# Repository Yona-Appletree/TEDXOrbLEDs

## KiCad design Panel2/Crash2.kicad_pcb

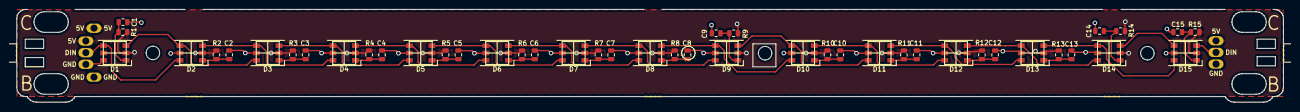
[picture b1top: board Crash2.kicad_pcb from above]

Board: 4 copper layers, 279.2 x 20.2 mm, 47 parts (0 on the bottom side), 33 nets.

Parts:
C1, C2, C3, C4, C5, C6, C7, C8, C9, C10, C11, C12, C13, C14, C15: 100NF; C_0805_2012Metric
D1, D2, D3, D4, D5, D6, D7, D8, D9, D10, D11, D12, D13, D14, D15: WS2813; LED_WS2812_PLCC6_5.0x5.0mm_P1.6mm
J1: IN; 1x3_18awgWireSolderPad-InsideStrut
J2: OUT; 1x3_18awgWireSolderPad-InsideStrut-OUT
R1, R2, R3, R4, R5, R6, R7, R8, R9, R10, R11, R12, R13, R14, R15: 330; R_0805_2012Metric

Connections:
+5V: D1.2, D2.2, D3.2, D4.2, D5.2, D6.2, D7.2, D8.2, D9.2, D10.2, D11.2, D12.2, D13.2, D14.2, D15.2, J1.1, J2.1, R1.1, R2.1, R3.1, R4.1, R5.1, R6.1, R7.1, R8.1, R9.1, R10.1, R11.1, R12.1, R13.1, R14.1, R15.1
GND: C1.2, C2.2, C3.2, C4.2, C5.2, C6.2, C7.2, C8.2, C9.2, C10.2, C11.2, C12.2, C13.2, C14.2, C15.2, D1.5, D1.6, D2.5, D3.5, D4.5, D5.5, D6.5, D7.5, D8.5, D9.5, D10.5, D11.5, D12.5, D13.5, D14.5, D15.5, J1.3, J2.3
unnamed: C1.1, D1.1, R1.2
unnamed: C2.1, D2.1, R2.2
unnamed: C3.1, D3.1, R3.2
unnamed: C4.1, D4.1, R4.2
unnamed: C5.1, D5.1, R5.2
unnamed: C6.1, D6.1, R6.2
unnamed: C7.1, D7.1, R7.2
unnamed: C8.1, D8.1, R8.2
unnamed: C9.1, D9.1, R9.2
unnamed: C10.1, D10.1, R10.2
unnamed: C11.1, D11.1, R11.2
unnamed: C12.1, D12.1, R12.2
unnamed: C13.1, D13.1, R13.2
unnamed: C14.1, D14.1, R14.2
unnamed: C15.1, D15.1, R15.2
unnamed: D1.3, D2.4, D3.6
unnamed: D1.4, D2.6, J1.2
unnamed: D2.3, D3.4, D4.6
unnamed: D3.3, D4.4, D5.6
unnamed: D4.3, D5.4, D6.6
unnamed: D5.3, D6.4, D7.6
unnamed: D6.3, D7.4, D8.6
unnamed: D7.3, D8.4, D9.6
unnamed: D10.3, D11.4, D12.6
unnamed: D9.3, D10.4, D11.6
unnamed: D8.3, D9.4, D10.6
unnamed: D11.3, D12.4, D13.6
unnamed: D12.3, D13.4, D14.6
unnamed: D13.3, D14.4, D15.6
unnamed: D14.3, D15.4
unnamed: D15.3, J2.2

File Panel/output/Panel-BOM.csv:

"Id","Designator","Package","Quantity","Designation","Supplier and ref",
4,"R2,R3,R4,R5,R6,R7,R8,R9,R10,R11,R12,R1,R13,R14,R15,R2,R3,R4,R5,R6,R7,R8,R9,R10,R11,R12,R16,R1,R13,R14,R15,R2,R3,R4,R5,R6,R7,R8,R9,R10,R11,R12,R16,R1,R13,R14,R15,R1,R13,R14,R15,R2,R3,R4,R5,R6,R7,R8,R9,R10,R11,R12,R2,R3,R4,R5,R6,R7,R8,R9,R10,R11,R12,R1,R13,R14,R15,R2,R3,R4,R5,R6,R7,R8,R9,R10,R11,R12,R16,R1,R13,R14,R15,R2,R3,R4,R5,R6,R7,R8,R9,R10,R11,R12,R16,R1,R13,R14,R15,R2,R3,R4,R5,R6,R7,R8,R9,R10,R11,R12,R1,R13,R14,R15,R16,R17,R2,R3,R4,R5,R6,R7,R8,R9,R10,R11,R12,R13,R14,R15,R16,R17,R1,R2,R3,R4,R5,R6,R7,R8,R9,R10,R11,R12,R16,R1,R13,R14,R15,R2,R3,R4,R5,R6,R7,R8,R9,R10,R11,R12,R16,R1,R13,R14,R15,R2,R3,R4,R5,R6,R7,R8,R9,R10,R11,R12,R1,R2,R3,R4,R5,R6,R7,R8,R9,R10,R11,R12,R1,R13,R14,R15,R1,R2,R3,R4,R5,R6,R7,R8,R9,R10,R11,R12","R_0805_2012Metric",214,"330",,,
5,"C7,C6,C5,C4,C3,C2,C1,C13,C14,C15,C8,C9,C10,C11,C12,C7,C6,C5,C4,C3,C2,C1,C13,C14,C15,C16,C8,C9,C10,C11,C12,C7,C6,C5,C4,C3,C2,C1,C10,C11,C12,C9,C15,C13,C14,C16,C8,C14,C13,C1,C3,C2,C4,C5,C6,C15,C8,C9,C10,C11,C12,C7,C7,C6,C5,C4,C3,C2,C1,C13,C14,C15,C8,C9,C10,C11,C12,C7,C6,C5,C4,C3,C2,C1,C13,C14,C15,C16,C8,C9,C10,C11,C12,C7,C6,C5,C4,C3,C2,C1,C15,C13,C14,C16,C8,C9,C10,C11,C12,C7,C6,C5,C4,C3,C2,C1,C13,C14,C15,C16,C17,C8,C9,C10,C11,C12,C7,C6,C5,C4,C3,C2,C1,C17,C13,C14,C15,C16,C8,C9,C10,C11,C12,C7,C6,C5,C4,C3,C2,C1,C13,C14,C15,C16,C8,C9,C10,C11,C12,C7,C6,C5,C4,C3,C2,C1,C13,C14,C15,C16,C8,C9,C10,C11,C12,C7,C6,C5,C4,C3,C2,C1,C7,C6,C5,C4,C3,C2,C1,C13,C14,C15,C8,C9,C10,C11,C12,C8,C9,C10,C11,C12,C7,C6,C5,C4,C3,C2,C1,C8,C9,C10,C11,C12","C_0805_2012Metric",214,"100NF",,,
7,"D14,D15,D13,D1,D2,D12,D11,D10,D9,D8,D7,D6,D5,D4,D3,D6,D5,D4,D3,D16,D15,D14,D13,D1,D2,D12,D11,D10,D9,D8,D7,D2,D12,D11,D10,D9,D8,D7,D6,D5,D4,D3,D1,D16,D15,D14,D13,D15,D14,D13,D1,D2,D12,D11,D10,D9,D8,D7,D6,D5,D4,D3,D15,D14,D13,D1,D2,D12,D11,D10,D9,D8,D7,D6,D5,D4,D3,D16,D15,D14,D13,D1,D2,D12,D11,D10,D9,D8,D7,D6,D5,D4,D3,D16,D15,D14,D13,D1,D2,D12,D11,D10,D9,D8,D7,D6,D5,D4,D3,D17,D16,D15,D14,D13,D1,D2,D12,D11,D10,D9,D8,D7,D6,D5,D4,D3,D17,D16,D15,D14,D13,D1,D2,D12,D11,D10,D9,D8,D7,D6,D5,D4,D3,D16,D15,D14,D13,D1,D2,D12,D11,D10,D9,D8,D7,D6,D5,D4,D3,D16,D15,D14,D13,D1,D2,D12,D11,D10,D9,D8,D7,D6,D5,D4,D3,D2,D12,D11,D10,D9,D8,D7,D6,D5,D4,D3,D14,D15,D13,D1,D2,D12,D11,D10,D9,D8,D7,D6,D5,D4,D3,D1,D2,D12,D11,D10,D9,D8,D7,D6,D5,D4,D3,D1","LED_WS2812_PLCC6_5.0x5.0mm_P1.6mm",214,"WS2813",,,
